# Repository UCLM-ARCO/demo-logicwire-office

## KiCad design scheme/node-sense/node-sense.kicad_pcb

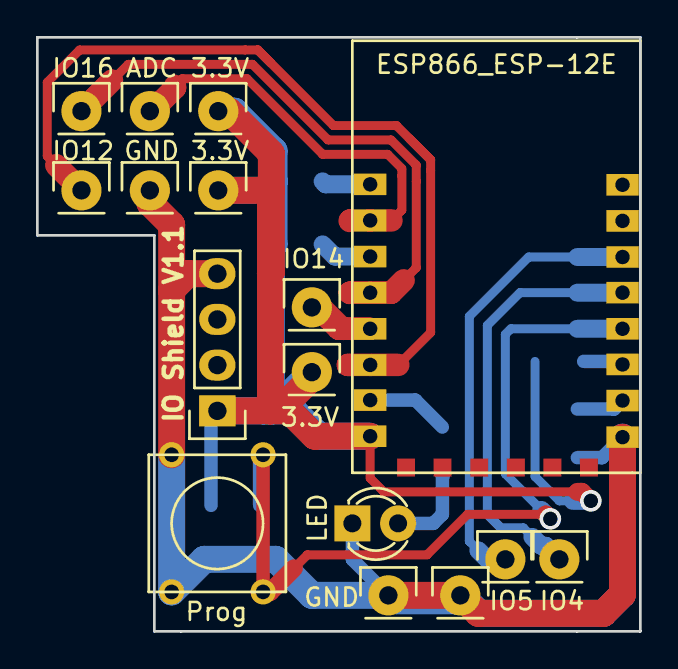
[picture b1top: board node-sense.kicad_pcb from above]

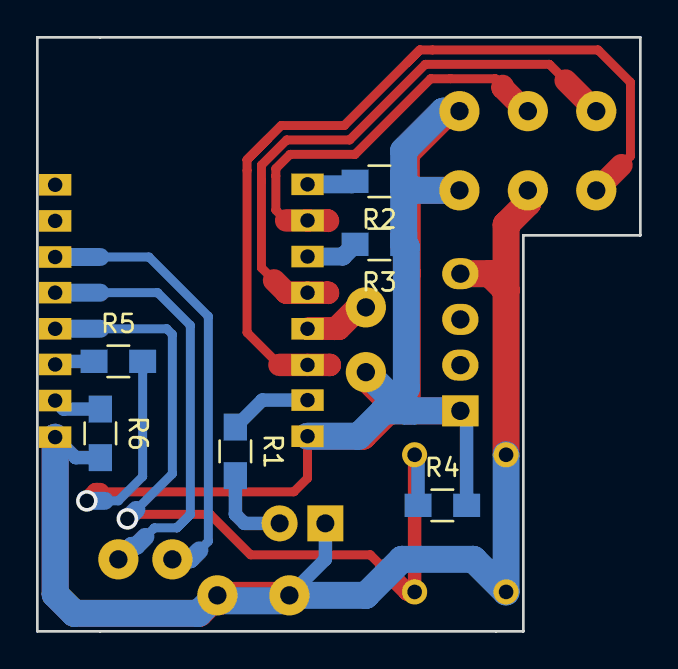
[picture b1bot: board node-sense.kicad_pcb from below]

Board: 2 copper layers, 33.5 x 33.0 mm, 22 parts (6 on the bottom side), 15 nets.

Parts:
D1: LED; LED-3MM
P1: Pin_Header_Straight_1x04
P2: IO16; Pin_Header_Straight_1x01
P3: IO14; Pin_Header_Straight_1x01
P4: IO12; Pin_Header_Straight_1x01
P6: IO4; Pin_Header_Straight_1x01
P8: IO5; Pin_Header_Straight_1x01
P9: ADC; Pin_Header_Straight_1x01
P10, P11, P15: GND; Pin_Header_Straight_1x01
P12, P13, P14: 3.3V; Pin_Header_Straight_1x01
R1: 1K; R_0805_HandSoldering
R2, R3, R4, R5, R6: 10K; R_0805_HandSoldering
SW1: Prog; SW_PUSH_SMALL
U1: ESP866_ESP-12E; ESP8266-12E

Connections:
/3.3Vcc: P1.1, P12.1, P13.1, P14.1, R2.1, R3.1, R4.2, R5.2, U1.8
/GND: D1.1, P1.4, P10.1, P11.1, P15.1, R6.2, SW1.2, U1.15
unnamed: D1.2, R1.2
unnamed: P2.1, U1.4
unnamed: P3.1, U1.5
unnamed: P4.1, U1.6
unnamed: P6.1, U1.19
unnamed: P8.1, U1.20
unnamed: P9.1, U1.2
unnamed: R1.1, U1.7
unnamed: R2.2, U1.1
unnamed: R3.2, U1.3
unnamed: R4.1, SW1.1, U1.18
unnamed: R5.1, U1.17
unnamed: R6.1, U1.16

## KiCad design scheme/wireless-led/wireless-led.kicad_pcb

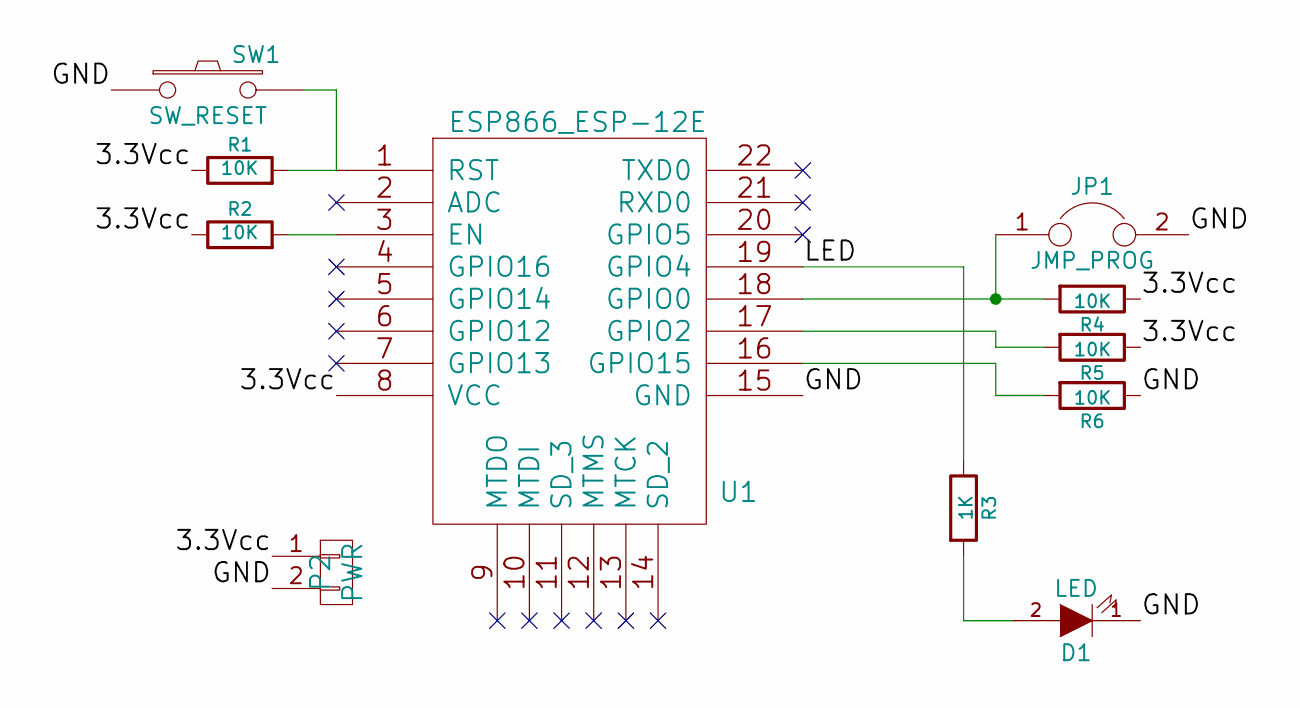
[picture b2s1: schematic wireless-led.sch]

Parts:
D1: LED; LED-3MM
JP1: JMP_PROG; Pin_Header_Straight_1x02
P2: PWR; Pin_Header_Straight_1x02
R1, R2, R4, R5, R6: 10K; R_0805_HandSoldering
R3: 1K; R_0805_HandSoldering
SW1: SW_RESET; SW_PUSH_SMALL
U1: ESP866_ESP-12E; ESP8266-12E

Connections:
/3.3Vcc: P2.1, R1.1, R2.1, R4.1, R5.1, U1.8 (VCC)
/GND: D1.1 (K), JP1.2, P2.2, R6.1, SW1.1, U1.15 (GND)
/LED: R3.1, U1.19 (GPIO4)
unnamed: D1.2 (A), R3.2
unnamed: JP1.1, R4.2, U1.18 (GPIO0)
unnamed: R1.2, SW1.2, U1.1 (RST)
unnamed: R2.2, U1.3 (EN)
unnamed: R5.2, U1.17 (GPIO2)
unnamed: R6.2, U1.16 (GPIO15)

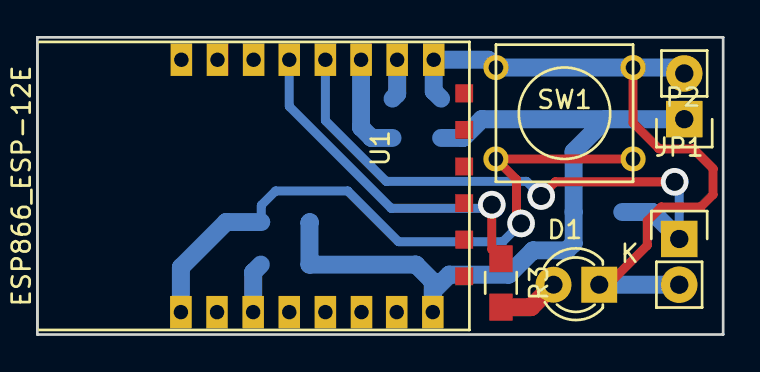
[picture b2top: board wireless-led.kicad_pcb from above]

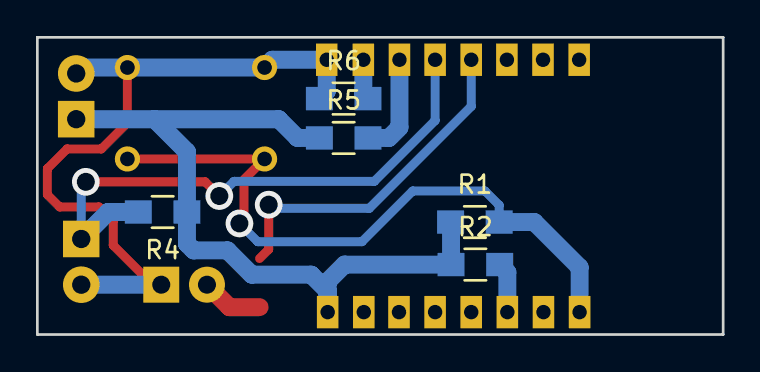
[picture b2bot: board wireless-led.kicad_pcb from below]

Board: 2 copper layers, 38.1 x 16.5 mm, 11 parts (5 on the bottom side), 9 nets.

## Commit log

2016-01-18 light-node: scheme done, working on PCB, not finished
2016-01-19 light-node: PCB done
2016-02-08 pcb: version 2, with a hole for USB charger
2016-02-10 light-node: upload last version
2016-02-10 light-node: panelized for dirtypcbs
2016-02-11 light-node: working on node code, not finished
2016-02-15 light-node: run as AP if wifi is not configured; add tool for configuring nodes
2016-02-16 light-node: node working
2016-02-19 Update client tool to accept IDM addr in form: 11:22
2016-02-22 port for sonoff module
2016-02-24 light-node: merge between Muffin and Sonoff
2016-02-24 switch-node: add basic features, working on notify observer
2016-02-25 switch-node: fix connection to AP issue
2016-02-25 switch-node: working
2016-02-29 android app: scan QR code to get config from URL on JSON format
2016-03-01 android: add icons for 'add' button; scan QR for add thing
2016-03-02 android: add Ice and DUO/IDM slices
2016-03-03 android: added support for DnD, action not completed
2016-03-09 add generated QR codes, working on DnD
2016-03-11 android: DnD, remove src item
2016-03-14 android: working with DnD for wiring, not finished
2016-03-15 android: basic DnD functionality working
2016-03-15 android: remove some comments
2016-03-16 android: retrieving props from server, not finished
2016-03-17 android: getting properties from PS
2016-04-04 android: setObserver almost working; sample-env: add button as service
2016-04-05 [closes #13] android: enable to remove observer
2016-04-05 android: swap sender/receiver positions
2016-04-05 android: do no set alfa of used receiver
2016-04-05 android: added arrow on links
2016-04-06 android: remove UTF-8 BOM from QR strings
2016-04-07 update node addressing; android: add launcher icon
2016-04-07 fix client parsing args
2016-04-08 media: add logic wiring logo
2016-04-08 android: working app
2016-04-08 android: avoid adding of repeated objects
2016-04-11 android: set observer from properties
2016-04-11 android: view/edit current settings
2016-04-11 smartButton: boilerplate
2016-04-13 SmartButton: minimal setup, button, advs, router usage: working
2016-04-13 SmartButton: show addr as QR code working, need push settings from mobile
2016-04-14 SmartButton: working on companion App, boilerplate
2016-04-14 SmartButton: companion app, not finished
2016-04-15 SmartButton, companion app: sync data with wearable; set properties on PS
2016-04-15 SmartButton, companion app: check that IDM address is valid
2016-04-15 SmartButton: add a note on code for remembering what's next
2016-04-18 SmartButton: finish sync with companion app
2016-04-19 SmartButton: set encoding version on invocations
2016-05-06 light-node: relocate functions, missing automatic forward declarations
2016-05-19 light-node: adapt to new io iface
2016-05-23 light-node: update client, use iot-node for config
2016-06-01 light: close relay on setup()
2016-06-04 light: avoid arduino-set-prefs makefile rule to fail
2016-06-06 wireless-led: add first release
2016-06-09 light: update NodeAdmin iface
2016-06-09 switch: update NodeAdmin iface
2016-06-09 node-switch: added remove logging
2016-06-15 LogicWiring: get WiringService from JSON
2016-06-16 [refs #37] logic-wiring: add support for multiple observers, using DUO Wiring Service
2016-06-16 logic-wiring: remove DEBUG code
2016-06-17 added wireless-led node (firmware src)
2016-06-20 tools: add set-properties for office objects; media: add qr-codes
2016-06-21 properties: set names on office objects
2016-07-13 [refs #41] added reed to a sonoff
2016-07-18 node-sense: add firmware
2016-07-18 node-sene: add more GND/Vcc pads, move tracks to front layer
2016-07-19 move node-sense to pcb.sonofff-io-shield repo
2016-07-19 rename node-sense to SPR-01
2016-07-21 small typo on doc
2016-07-21 SPR-01: add T_HOLD and T_MIN params to PIR detection alg
2016-07-26 logicwiring: update SDK
2016-07-28 move config.h.in to config.h
2016-10-19 Update some pintout definitions
2016-11-09 switch-node: IDM.Address moved to DUO, updating
2020-04-07 Notes for master
